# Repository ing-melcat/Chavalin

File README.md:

# Seguidor de Línea Pro v1 (ESP32-C3 + 16 Sensores + EDF 2S)

Proyecto de robot seguidor de línea velocista de 16 sensores basado en **ESP32-C3 SuperMini**, multiplexor analógico **CD74HC4067**, dos barras de sensores **QTR-8A** (versión china) dispuestas en **V (22°)**, driver de motores **TB6612FNG**, motores **JSumo 12V 3600 RPM**, llantas de silicón **Ø20 mm** y turbina **EDF 30 mm 14000KV** con alimentación independiente **2S (7.4V)**.

> **100% Libre de Wi-Fi / Bluetooth / RF:** Todo el proyecto opera de forma autónoma para cumplir el reglamento **RoboTiger Velocista Pro**. La calibración en banco y el ajuste fino de parámetros se realizan por **USB Serial (115200 baud)** con guardado automático en **Flash NVS (`Preferences`)**.

---

## Estructura del Repositorio

| Carpeta / Archivo | Descripción |
| :--- | :--- |
| `seguidor_pro/seguidor_pro.ino` | **Firmware único** de competencia (500 Hz exactos, `dt = 2 ms`), consola USB Serial de calibración/diagnóstico y persistencia NVS. |
| `test_turbina_nano/` | Sketch auxiliar de prueba PWM para ESC de turbina en Arduino Nano. |
| `v1/` | Esquemático y PCB base en KiCad (`v1.kicad_sch`, `v1.kicad_pcb`). |
| `v1_enrutado/` | PCB enrutado y vistas 3D de referencia. |

---

## Especificaciones de Hardware y Mapeo de Pines

- **Microcontrolador:** ESP32-C3 SuperMini (`esp32:esp32:nologo_esp32c3_super_mini`, `USB CDC On Boot = Enabled`).
- **Tracción:** 2× motores **JSumo 12V 3600 RPM**, rines de aluminio **Ø12 × 33 mm** (eje 3 mm) + gomas de silicón **Ø20 × 28 mm** (`Ø externa = 20 mm`).
- **Alimentación Principal (Tracción y Lógica):** LiPo **12V 750 mAh** directo a `VM` del TB6612 + regulador **step-down 12V→5V 3A** para alimentar el ESP32-C3.
- **Sistema Aerodinámico (Independiente):** Turbina **EDF 30 mm 14000KV** (~224 gf / 2.20 N de empuje máx.) + **ESC 35A** alimentados por batería aparte **7.4V (2S) 450 mAh** (cable rojo BEC del ESC desconectado; **GND común** con la placa).

| Subsistema | Señal / Función | Pin ESP32-C3 | Notas |
| :--- | :--- | :--- | :--- |
| **TB6612 (LEDC 20 kHz, 8 bits)** | `AI1` / `AI2` (Motor Izq A) | **GPIO 1**, **GPIO 2** | `PWMA`, `PWMB`, `STBY` fijos a `3.3V` |
| **TB6612 (LEDC 20 kHz, 8 bits)** | `BI1` / `BI2` (Motor Der B) | **GPIO 3**, **GPIO 8** | `GPIO 8` comparte LED azul integrado |
| **CD74HC4067 (Mux 16 ch)** | `SIG` / `COM` (Entrada ADC) | **GPIO 0** | Pull-down interno 45 kΩ forzado por registro |
| **CD74HC4067 (Mux 16 ch)** | `S0`, `S1`, `S2`, `S3` | **GPIO 20, 10, 7, 6** | `S0=20, S1=10, S2=7, S3=6`; `EN` (`~E`) fijo a `GND` |
| **Barras 2× QTR-8A (V 22°)** | `LED_ON` (Emisores IR) | **GPIO 4** | `HIGH` activo; `CH00..07` Barra 1, `CH08..15` Barra 2 |
| **Turbina EDF (LEDC 50 Hz)** | Señal PWM ESC (1000–2000 µs) | **GPIO 5** | Resolución 14 bits; armado seguro en `1000 µs` (0%) |
| **Arrancador Juez RRT** | Señal `GO` (`5V, GND, GO, RDY`) | **GPIO 21** | `INPUT_PULLDOWN`, antirrebote 3 lecturas a 500 Hz |
| **Calibración en Pista** | Botón físico `BOOT_CAL` | **GPIO 9** | `INPUT_PULLUP` (botón `BOOT` integrado) |

---

## Detalles Críticos de Ingeniería

1. **Anti-Saturación ADC en ESP32-C3 (`4095` Fijo):**
   El ADC con `ADC_11db` satura a **`2922 mV`**, mientras que las barras QTR-8A chinas tienen pull-ups (~15 kΩ a 3.3V) que las dejan entre `3.0 V` y `3.3 V`. En Arduino ESP32 v3.x, `analogReadMilliVolts()` reconfigura el pin y borra `pinMode(..., INPUT_PULLDOWN)`. Por ello el código ejecuta en `setup()`:
   - `analogReadMilliVolts(PIN_SIG);`
   - `gpio_pullup_dis((gpio_num_t)PIN_SIG);`
   - `gpio_pulldown_en((gpio_num_t)PIN_SIG);`
   Esto forma un divisor de voltaje (~`2483 mV` en reposo) dentro de la zona lineal del ADC.

2. **USB CDC No Bloqueante en Pista (`dt = 2 ms`):**
   Sin laptop conectada, escribir al puerto serie en ESP32-C3 puede bloquear el lazo de 500 Hz. El firmware usa `Serial.setTxTimeoutMs(0)`, verificación previa `Serial.availableForWrite()` y **pausa la telemetría periódica automáticamente durante la carrera**.

3. **Constantes Calibradas por Simulación Física (JSumo 3600 RPM + Ø20 mm + EDF 2S, 7/7 Escenarios):**
   Valores por defecto cargados cuando NVS está vacío (o al ejecutar `reset`):
   - `vr = 95` (velocidad recta), `vc = 58` (velocidad mínima en curva), `kf = 175` (freno en curva), `K_FRENO_DYN = 3.0`, `BRAKE_CAP = -195.0`, `MAX_PID = 175.0`.
   - `kpb = 0.34`, `kpc = 0.56` (ganancia cuadrática), `kd = 0.014` (`Kd_step = 7.00` a 2 ms, `ALPHA_D = 0.20`).
   - `tb = 50%` (recta), `tc = 80%` (curva cerrada), rampa de entrada 200 ms, decaimiento 160 ms (limitado a `[20%, 100%]` para no apagar la turbina en carrera).

---

## Compilación y Carga

- **Placa en Arduino IDE:** `NOLOGO ESP32C3 Super Mini` (`esp32:esp32:nologo_esp32c3_super_mini`)
- **USB CDC On Boot:** `Enabled` (`CDCOnBoot=cdc`)
- **Puerto:** `COM5` (o el COM asignado al conectar por USB-C)
- **Archivo único a abrir:** `seguidor_pro/seguidor_pro.ino`

---

## Calibración y Ajuste Fino por USB Serial (`115200 baud`)

Al conectar el robot a la PC (Monitor Serial a **115200**, funciona con `"Nueva línea"` o `"Sin ajuste de línea"`), dispones de consola interactiva sin recompilar:

| Comando | Acción |
| :--- | :--- |
| `c` | Autocalibra la base de los 16 sensores (percentil 75, ~1.2 s). Equivalente en pista al botón **`BOOT` (GPIO 9)**. |
| `v` | Activa / pausa la telemetría en vivo cada 250 ms (`S:[########|........] Err:+000 Turb: 0% GO:0`). |
| `t` (o `m`) | Test completo de motores (cuenta regresiva 3 s: A adelante, B adelante, ambos, reversa, giro en eje). |
| `1` / `2` | Prueba rápida 1 s solo Motor A (Izq) o Motor B (Der). |
| `u` | Prueba segura de turbina EDF al **25% durante 1.5 s** (sujetar robot; desconectar en `0%`). |
| `l` | Activa / desactiva el seguidor en banco (500 Hz + turbina). **Usar con el robot levantado o en pista controlada.** |
| `s` | **PARO DE EMERGENCIA inmediato** (detiene motores y apaga turbina al 0%, incluso en medio de una prueba o señal `GO`). |
| `p` o `?` | Muestra los parámetros actuales guardados en Flash NVS y el resumen de comandos. |
| `vr=95`, `vc=58`, `kf=175` | Ajusta velocidades / freno y guarda automáticamente en **Flash NVS**. |
| `kpb=0.34`, `kpc=0.56`, `kd=0.014` | Ajusta ganancias del PID dinámico y guarda automáticamente en **Flash NVS**. |
| `tb=50`, `tc=80` | Ajusta potencia base/curva de la turbina EDF (`20%..100%`) y guarda en **Flash NVS**. |
| `reset` | Restaura todas las constantes calibradas por defecto (`3600 RPM / Ø20 mm`) en Flash NVS. |

### Secuencia en Pista (Competencia)
1. Encender baterías (ESP32 arma el ESC de la turbina a `1000 µs` en `1 s` y realiza una autocalibración inicial).
2. Colocar el robot sobre el fondo de la pista y presionar **`BOOT` (GPIO 9)** si se requiere recalibrar la luz del coliseo (toma ~1.2 s, dentro de los 15 s previos).
3. Conectar o esperar señal positiva **`GO` (`GPIO 21`)** del módulo arrancador RRT del juez: el robot arranca en el lazo determinista de 500 Hz con turbina encendida y se detiene con freno activo cuando `GO` vuelve a `LOW`.

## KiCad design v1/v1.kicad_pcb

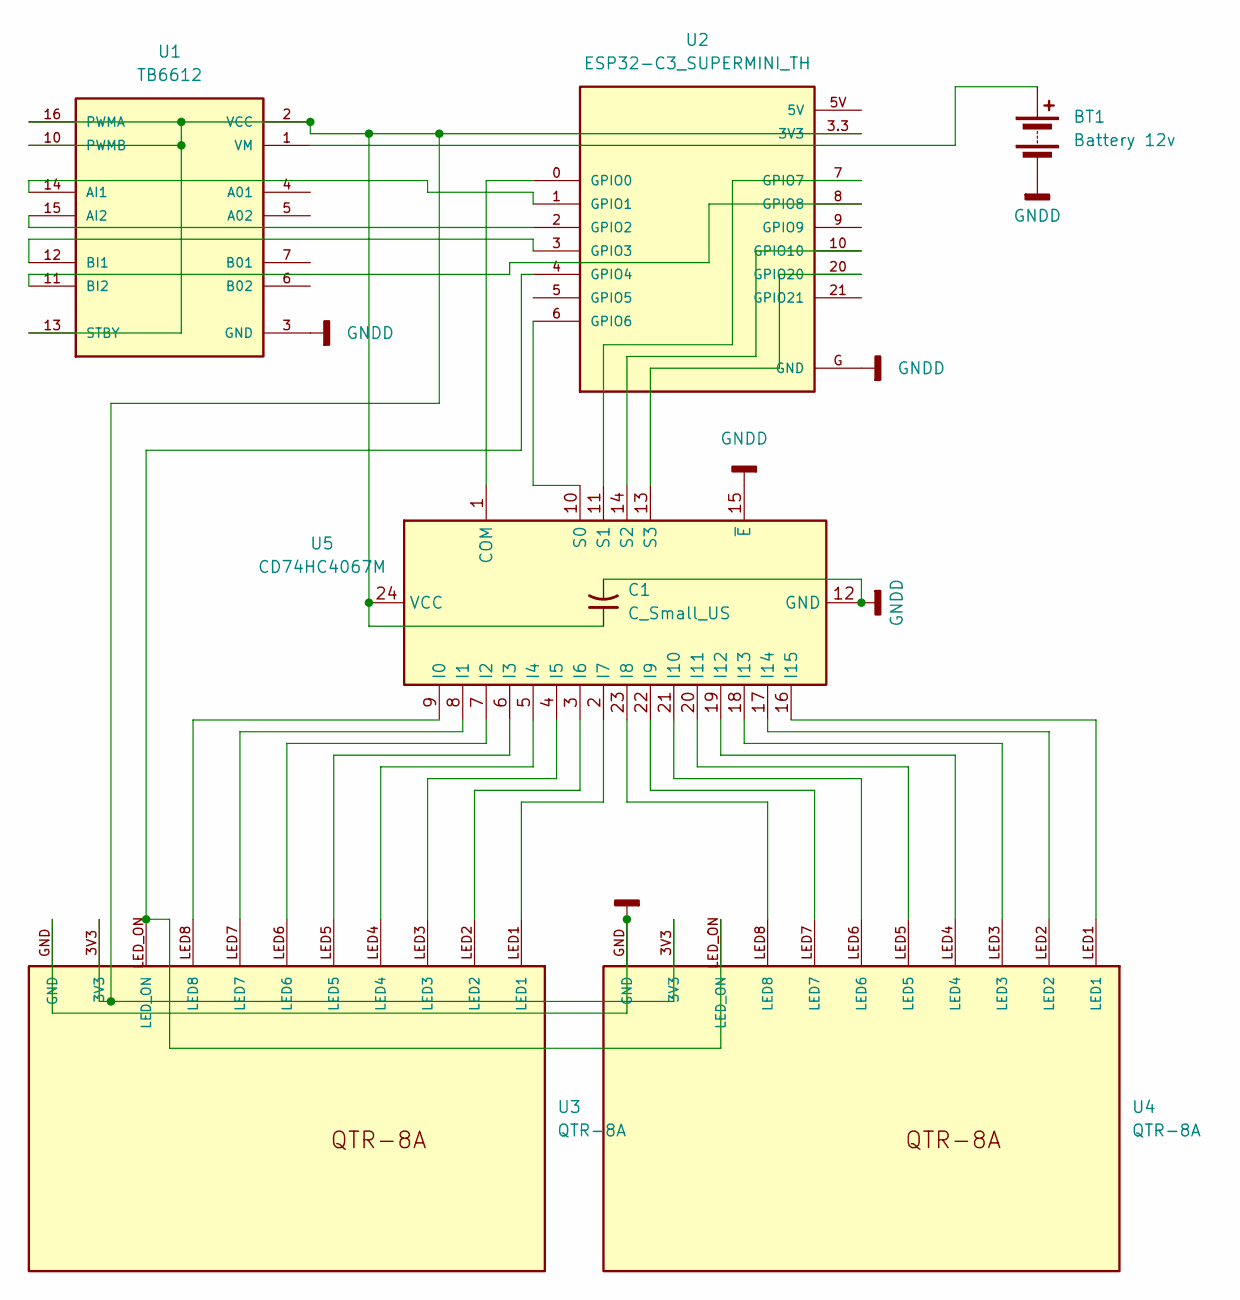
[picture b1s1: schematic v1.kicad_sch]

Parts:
BT1: Battery 12v; QFN-40-1EP_6x6mm_P0.5mm_EP4.6x4.6mm
C1: C_Small_US; SOIC-8_3.9x4.9mm_P1.27mm
U1: TB6612; MODULE_ROB-14450; MPN ROB-14450
U2: ESP32-C3_SUPERMINI_TH; MODULE_ESP32-C3_SUPERMINI_TH; MPN ESP32-C3 SuperMini_TH
U3, U4: QTR-8A; MPN QTR-8A
U5: CD74HC4067M; SOIC-24W_7.5x15.4mm_P1.27mm

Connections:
GNDD: BT1.2 (-), C1.2, U1.3 (GND), U1.8 (GND), U1.9 (GND), U2.G (GND), U3.GND, U4.GND, U5.12 (GND), U5.15 (~E)
unnamed: BT1.1 (+), U1.1 (VM)
unnamed: U1.14 (AI1), U2.1 (GPIO1)
unnamed: U1.15 (AI2), U2.2 (GPIO2)
unnamed: U1.12 (BI1), U2.3 (GPIO3)
unnamed: U1.11 (BI2), U2.8 (GPIO8)
unnamed: C1.1, U1.2 (VCC), U1.10 (PWMB), U1.13 (STBY), U1.16 (PWMA), U2.3.3 (3V3), U3.3V3, U4.3V3, U5.24 (VCC)
unnamed: U2.0 (GPIO0), U5.1 (COM)
unnamed: U2.4 (GPIO4), U3.LED_ON, U4.LED_ON
unnamed: U2.6 (GPIO6), U5.10 (S0)
unnamed: U2.7 (GPIO7), U5.11 (S1)
unnamed: U2.10 (GPIO10), U5.14 (S2)
unnamed: U2.20 (GPIO20), U5.13 (S3)
unnamed: U3.LED8, U5.9 (I0)
unnamed: U3.LED7, U5.8 (I1)
unnamed: U3.LED6, U5.7 (I2)
unnamed: U3.LED5, U5.6 (I3)
unnamed: U3.LED4, U5.5 (I4)
unnamed: U3.LED3, U5.4 (I5)
unnamed: U3.LED2, U5.3 (I6)
unnamed: U3.LED1, U5.2 (I7)
unnamed: U4.LED8, U5.23 (I8)
unnamed: U4.LED7, U5.22 (I9)
unnamed: U4.LED6, U5.21 (I10)
unnamed: U4.LED5, U5.20 (I11)
unnamed: U4.LED4, U5.19 (I12)
unnamed: U4.LED3, U5.18 (I13)
unnamed: U4.LED2, U5.17 (I14)
unnamed: U4.LED1, U5.16 (I15)

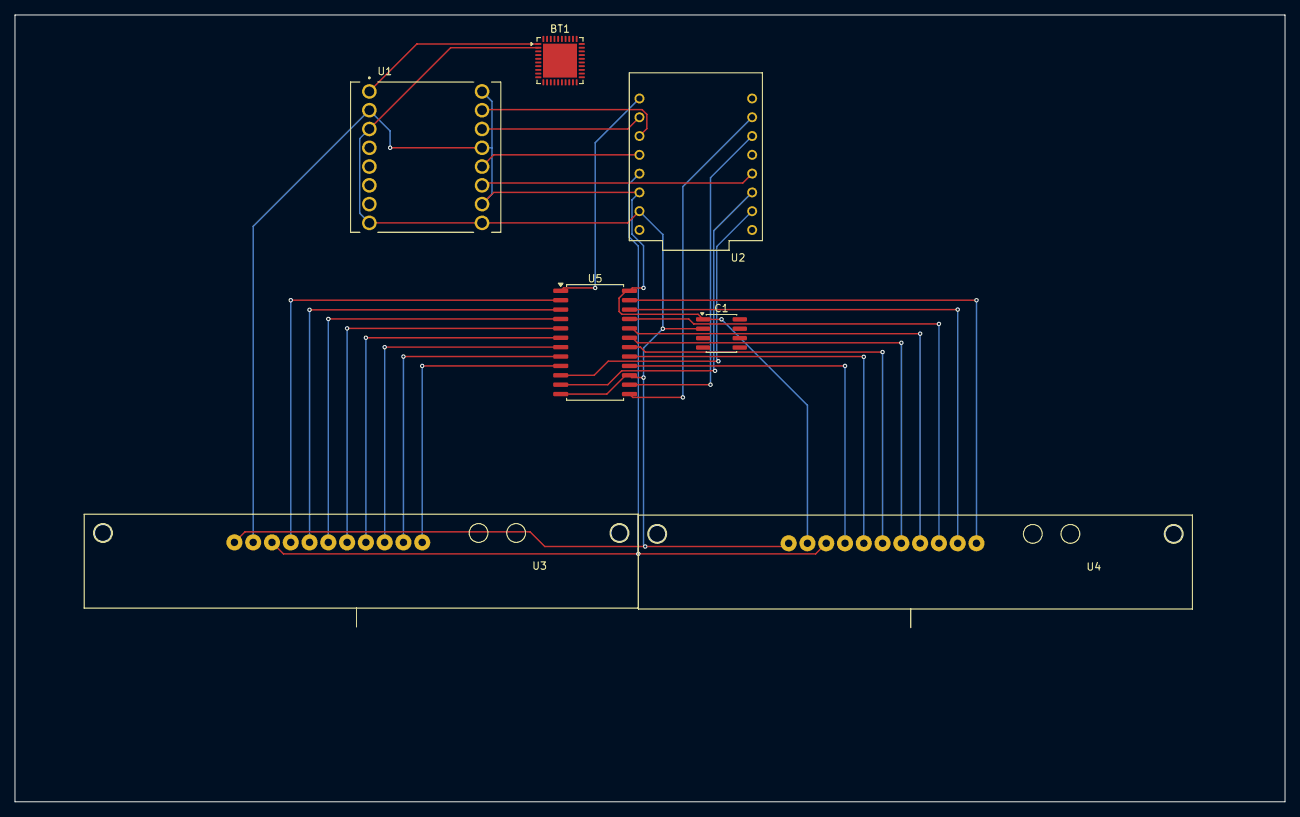
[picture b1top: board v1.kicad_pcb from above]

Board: 2 copper layers, 171.8 x 106.4 mm, 7 parts (0 on the bottom side), 29 nets.

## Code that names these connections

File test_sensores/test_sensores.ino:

/*
  =============================================================================
  PROYECTO: SEGUIDOR DE LINEA PRO - TEST DE SENSORES CON ANTI-SATURACIÓN ADC
  =============================================================================
  SOLUCIÓN AL PROBLEMA DE "TODO EN 4095":
  - El ADC del ESP32-C3 satura (topa en 4095) a los 2922 mV (2.92V).
  - Tus barras de sensores tienen resistencias pull-up a 3.3V (~15 kOhm), lo que
    mantiene el voltaje en reposo cerca de 3.30V (encima del tope de 2.92V).
  - Por eso, aunque el sensor baje de 3.30V a 2.95V al detectar color/luz, el
    ADC sin carga sigue marcando 4095 fijo.
  - Al mantener activo el Pull-Down interno de 45 kOhm por registro de hardware
    (gpio_pulldown_en) durante la conversión ADC, formamos un divisor de tensión
    que baja el reposo a ~2480 mV (dentro del rango lineal del ADC) y permite
    ver cualquier cambio en cada sensor.
  =============================================================================
*/

#include "driver/gpio.h"

#define PIN_SIG      0   // GPIO0: Entrada analógica conectada a SIG (COM) del Mux
#define PIN_S0      20   // GPIO20: Selector S0
#define PIN_S1      10   // GPIO10: Selector S1
#define PIN_S2       7   // GPIO7: Selector S2
#define PIN_S3       6   // GPIO6: Selector S3
#define PIN_LED_ON   4   // GPIO4: Encendido de emisores IR

// Sensibilidad en milivoltios respecto al reposo para marcar detección [█]
const int SENSIBILIDAD_MV = 20;

uint16_t lecturas_mv[16];
uint16_t base_mv[16];
bool calibrado = false;

void seleccionarCanal(uint8_t canal) {
  digitalWrite(PIN_S0, (canal & 0x01) ? HIGH : LOW);
  digitalWrite(PIN_S1, (canal & 0x02) ? HIGH : LOW);
  digitalWrite(PIN_S2, (canal & 0x04) ? HIGH : LOW);
  digitalWrite(PIN_S3, (canal & 0x08) ? HIGH : LOW);
  delayMicroseconds(30);
}

void leerSensoresMV() {
  // Asegurar que el Pull-Down de 45k esté activo en el pad para evitar saturación a 4095
  gpio_pullup_dis((gpio_num_t)PIN_SIG);
  gpio_pulldown_en((gpio_num_t)PIN_SIG);

  for (uint8_t ch = 0; ch < 16; ch++) {
    seleccionarCanal(ch);
    delayMicroseconds(100);
    // Promediar 4 muestras rápidas para eliminar ruido
    uint32_t suma = 0;
    for (int m = 0; m < 4; m++) {
      suma += analogReadMilliVolts(PIN_SIG);
    }
    lecturas_mv[ch] = suma / 4;
  }
}

void calibrarBase() {
  for (int i = 0; i < 16; i++) base_mv[i] = 0;
  for (int muestra = 0; muestra < 10; muestra++) {
    leerSensoresMV();
    for (int i = 0; i < 16; i++) {
      base_mv[i] += lecturas_mv[i];
    }
    delay(20);
  }
  for (int i = 0; i < 16; i++) {
    base_mv[i] /= 10;
  }
  calibrado = true;
}

void setup() {
  Serial.begin(115200);
  delay(1000);

  pinMode(PIN_S0, OUTPUT);
  pinMode(PIN_S1, OUTPUT);
  pinMode(PIN_S2, OUTPUT);
  pinMode(PIN_S3, OUTPUT);

  pinMode(PIN_LED_ON, OUTPUT);
  digitalWrite(PIN_LED_ON, HIGH);

  analogReadResolution(12);
  analogSetAttenuation(ADC_11db);

  // Inicializar el bus ADC en PIN_SIG primero y luego activar el Pull-Down por hardware
  analogReadMilliVolts(PIN_SIG);
  gpio_pullup_dis((gpio_num_t)PIN_SIG);
  gpio_pulldown_en((gpio_num_t)PIN_SIG);

  calibrarBase();
}

void loop() {
  leerSensoresMV();

  // Si el cable SIG se desconecta, con el Pull-Down caerá por debajo de 100 mV
  if (lecturas_mv[0] < 150 && lecturas_mv[7] < 150 && lecturas_mv[15] < 150) {
    Serial.println("[!] CABLE SIG DESCONECTADO O MUX SIN ALIMENTACION (Lectura: 0 mV)");
    delay(500);
    return;
  }

  Serial.println("------------------------------------------------------------------------------------------------------------------");
  Serial.println("CANAL:  | CH00  CH01  CH02  CH03  CH04  CH05  CH06  CH07 | CH08  CH09  CH10  CH11  CH12  CH13  CH14  CH15 |");
  Serial.println("SENSOR: | U3_S8 U3_S7 U3_S6 U3_S5 U3_S4 U3_S3 U3_S2 U3_S1 | U4_S8 U4_S7 U4_S6 U4_S5 U4_S4 U4_S3 U4_S2 U4_S1 |");
  Serial.println("------------------------------------------------------------------------------------------------------------------");

  // Mostrar voltaje real en mV (ya sin saturar en 4095)
  Serial.print("mV:     | ");
  for (int i = 0; i < 16; i++) {
    Serial.printf("%4d  ", lecturas_mv[i]);
    if (i == 7) Serial.print("| ");
  }
  Serial.println("|");

  // Mostrar diferencia (Delta) respecto al reposo
  Serial.print("CAMBIO: | ");
  for (int i = 0; i < 16; i++) {
    int diff = (int)lecturas_mv[i] - (int)base_mv[i];
    Serial.printf("%+4d  ", diff);
    if (i == 7) Serial.print("| ");
  }
  Serial.println("|");

  // Indicador visual cuando hay variación en el sensor
  Serial.print("DETECT: | ");
  for (int i = 0; i < 16; i++) {
    int diff = abs((int)lecturas_mv[i] - (int)base_mv[i]);
    if (diff >= SENSIBILIDAD_MV || lecturas_mv[i] < 2000) {
      Serial.print(" [█]  ");
    } else {
      Serial.print("  .   ");
    }
    if (i == 7) Serial.print("| ");
  }
  Serial.println("|");
  Serial.println("------------------------------------------------------------------------------------------------------------------\n");

  delay(200);
}

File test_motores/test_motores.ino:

/*
  =============================================================================
  TEST EXCLUSIVO DE MOTORES (TB6612FNG + ESP32-C3 SUPERMINI)
  =============================================================================
  Mapeo de pines (v1.kicad_sch):
    - AI1 (Motor Izquierdo / A) -> GPIO 1
    - AI2 (Motor Izquierdo / A) -> GPIO 2
    - BI1 (Motor Derecho / B)   -> GPIO 3
    - BI2 (Motor Derecho / B)   -> GPIO 8 (comparte con LED azul de la placa)
    - PWMA, PWMB, STBY          -> Fijos a 3.3V por hardware en PCB

  Método de control (PWM LEDC 20 kHz, 8 bits: 0..255):
    - Adelante: IN1 = PWM, IN2 = 0
    - Reversa:  IN1 = 0,   IN2 = PWM
    - Freno:    IN1 = 255, IN2 = 255
    - Paro:     IN1 = 0,   IN2 = 0

  Funcionamiento:
    - Inicia en modo MANUAL seguro (motores detenidos al arrancar).
    - Comandos por Monitor Serial (115200 baud):
        '1' -> Motor A (Izquierdo) ADELANTE (1.5 s)
        '2' -> Motor A (Izquierdo) REVERSA  (1.5 s)
        '3' -> Motor B (Derecho)   ADELANTE (1.5 s)
        '4' -> Motor B (Derecho)   REVERSA  (1.5 s)
        'w' -> AMBOS motores ADELANTE (1.5 s)
        'r' -> AMBOS motores REVERSA  (1.5 s)
        '+' / '-' -> Subir / bajar PWM de prueba (80..240)
        't' -> Iniciar ciclo automatico (5 fases)
        's' -> Paro inmediato / pausar ciclo
        'h' -> Mostrar menu de comandos
  =============================================================================
*/

#include <Arduino.h>

#define PIN_MOT_A1  1   // AI1: Motor Izquierdo (A)
#define PIN_MOT_A2  2   // AI2: Motor Izquierdo (A)
#define PIN_MOT_B1  3   // BI1: Motor Derecho (B)
#define PIN_MOT_B2  8   // BI2: Motor Derecho (B) - LED azul integrado

// Por seguridad mantenemos la turbina en 0% (1000 us) si el ESC está conectado en GPIO 5
#define PIN_TURBINA 5

const uint32_t PWM_FREQ = 20000;
const uint8_t  PWM_RES  = 8;

bool ciclo_automatico = false;
int  pwm_test = 160;
int  curA = 0;
int  curB = 0;

void setMotorA(int speed) {
  speed = constrain(speed, -255, 255);
  // Motor A (Izq) tiene polaridad física invertida en cableado: adelante = AI2 PWM
  if (speed > 0) {
    ledcWrite(PIN_MOT_A1, 0);
    ledcWrite(PIN_MOT_A2, speed);
  } else if (speed < 0) {
    ledcWrite(PIN_MOT_A1, -speed);
    ledcWrite(PIN_MOT_A2, 0);
  } else {
    ledcWrite(PIN_MOT_A1, 0);
    ledcWrite(PIN_MOT_A2, 0);
  }
}

void setMotorB(int speed) {
  speed = constrain(speed, -255, 255);
  if (speed > 0) {
    ledcWrite(PIN_MOT_B1, speed);
    ledcWrite(PIN_MOT_B2, 0);
  } else if (speed < 0) {
    ledcWrite(PIN_MOT_B1, 0);
    ledcWrite(PIN_MOT_B2, -speed);
  } else {
    ledcWrite(PIN_MOT_B1, 0);
    ledcWrite(PIN_MOT_B2, 0);
  }
}

void setMotors(int speedA, int speedB) {
  setMotorA(speedA);
  setMotorB(speedB);
}

void stopMotors() {
  setMotors(0, 0);
  curA = 0;
  curB = 0;
}

void irSuaveMotores(int tgtA, int tgtB) {
  while (curA != tgtA || curB != tgtB) {
    int nextA = tgtA;
    int nextB = tgtB;
    if ((curA > 0 && tgtA < 0) || (curA < 0 && tgtA > 0)) nextA = 0;
    if ((curB > 0 && tgtB < 0) || (curB < 0 && tgtB > 0)) nextB = 0;

    if (curA < nextA) curA = min(nextA, curA + 20);
    else if (curA > nextA) curA = max(nextA, curA - 20);

    if (curB < nextB) curB = min(nextB, curB + 20);
    else if (curB > nextB) curB = max(nextB, curB - 20);

    setMotors(curA, curB);
    delay(20);
  }
}

void brakeMotors() {
  ledcWrite(PIN_MOT_A1, 255);
  ledcWrite(PIN_MOT_A2, 255);
  ledcWrite(PIN_MOT_B1, 255);
  ledcWrite(PIN_MOT_B2, 255);
}

// Espera verificando si el usuario envía 's' para abortar al instante
bool esperarConAborto(uint32_t ms) {
  uint32_t inicio = millis();
  while (millis() - inicio < ms) {
    while (Serial.available() > 0) {
      char c = (char)Serial.read();
      if (c == 's' || c == 'S') {
        stopMotors();
        ciclo_automatico = false;
        Serial.println("\n>> [ALTO] Motores detenidos. Envia 't' para reanudar o '1'/'2'.");
        return false;
      }
    }
    delay(10);
  }
  return true;
}

void ejecutarSecuenciaMotores() {
  Serial.println("\n------------------------------------------------------");
  Serial.println(">> [1/5] MOTOR A (Izquierdo: GPIO 1/2) -> ADELANTE (PWM 140)");
  irSuaveMotores(140, 0);
  if (!esperarConAborto(1500)) return;
  irSuaveMotores(0, 0);
  if (!esperarConAborto(500)) return;

  Serial.println(">> [2/5] MOTOR A (Izquierdo: GPIO 1/2) -> REVERSA  (PWM -140)");
  irSuaveMotores(-140, 0);
  if (!esperarConAborto(1500)) return;
  irSuaveMotores(0, 0);
  if (!esperarConAborto(500)) return;

  Serial.println(">> [3/5] MOTOR B (Derecho:   GPIO 3/8) -> ADELANTE (PWM 140)");
  irSuaveMotores(0, 140);
  if (!esperarConAborto(1500)) return;
  irSuaveMotores(0, 0);
  if (!esperarConAborto(500)) return;

  Serial.println(">> [4/5] MOTOR B (Derecho:   GPIO 3/8) -> REVERSA  (PWM -140)");
  irSuaveMotores(0, -140);
  if (!esperarConAborto(1500)) return;
  irSuaveMotores(0, 0);
  if (!esperarConAborto(500)) return;

  Serial.println(">> [5/5] AMBOS MOTORES -> ADELANTE (PWM 160) + PARO SUAVE");
  irSuaveMotores(160, 160);
  if (!esperarConAborto(1500)) return;
  irSuaveMotores(0, 0);
  stopMotors();
  Serial.println(">> [OK] Ciclo terminado. Repitiendo en 3 s ('s' para detener)...");
}

void imprimirMenu() {
  Serial.println("\n======================================================");
  Serial.println("  TEST MANUAL DE MOTORES TB6612 - ESP32-C3 (COM5)");
  Serial.println("  Motor A (Izq): AI1=GPIO1, AI2=GPIO2");
  Serial.println("  Motor B (Der): BI1=GPIO3, BI2=GPIO8");
  Serial.printf ("  PWM actual: %d / 255 ('+' / '-' para ajustar)\n", pwm_test);
  Serial.println("  ------------------------------------------------------");
  Serial.println("  '1' = Motor IZQ ADELANTE | '2' = Motor IZQ REVERSA");
  Serial.println("  '3' = Motor DER ADELANTE | '4' = Motor DER REVERSA");
  Serial.println("  'w' = AMBOS ADELANTE     | 'r' = AMBOS REVERSA");
  Serial.println("  't' = Ciclo automatico   | 's' = PARO INMEDIATO");
  Serial.println("  'h' = Mostrar este menu");
  Serial.println("======================================================");
}

void probarManual(const char* desc, int sA, int sB, uint32_t ms) {
  ciclo_automatico = false;
  Serial.printf(">> [MANUAL PWM=%d] %s\n", pwm_test, desc);
  irSuaveMotores(sA, sB);
  if (esperarConAborto(ms)) {
    irSuaveMotores(0, 0);
    stopMotors();
    Serial.println(">> Detenido.");
  }
}

void setup() {
  Serial.begin(115200);
  Serial.setTxTimeoutMs(50);

  ledcAttach(PIN_MOT_A1, PWM_FREQ, PWM_RES);
  ledcAttach(PIN_MOT_A2, PWM_FREQ, PWM_RES);
  ledcAttach(PIN_MOT_B1, PWM_FREQ, PWM_RES);
  ledcAttach(PIN_MOT_B2, PWM_FREQ, PWM_RES);
  stopMotors();

  // Mantener ESC de turbina en 1000 us (0%) por seguridad
  ledcAttach(PIN_TURBINA, 50, 14);
  ledcWrite(PIN_TURBINA, (1000UL * 16383UL) / 20000UL);

  delay(1500);
  imprimirMenu();
  Serial.println("Modo MANUAL listo (motores detenidos). Envia un comando:");
}

void loop() {
  while (Serial.available() > 0) {
    char c = (char)Serial.read();
    if (c == 's' || c == 'S') {
      stopMotors();
      ciclo_automatico = false;
      Serial.println(">> [ALTO] Motores detenidos (PWM=0).");
    } else if (c == 't' || c == 'T') {
      ciclo_automatico = true;
      Serial.println(">> [AUTO] Iniciando ciclo automatico de motores...");
    } else if (c == '1') {
      probarManual("Motor A (Izquierdo) ADELANTE (1.5 s)...", pwm_test, 0, 1500);
    } else if (c == '2') {
      probarManual("Motor A (Izquierdo) REVERSA  (1.5 s)...", -pwm_test, 0, 1500);
    } else if (c == '3') {
      probarManual("Motor B (Derecho) ADELANTE (1.5 s)...", 0, pwm_test, 1500);
    } else if (c == '4') {
      probarManual("Motor B (Derecho) REVERSA  (1.5 s)...", 0, -pwm_test, 1500);
    } else if (c == 'w' || c == 'W') {
      probarManual("AMBOS motores ADELANTE (1.5 s)...", pwm_test, pwm_test, 1500);
    } else if (c == 'r' || c == 'R') {
      probarManual("AMBOS motores REVERSA  (1.5 s)...", -pwm_test, -pwm_test, 1500);
    } else if (c == '+') {
      pwm_test = constrain(pwm_test + 20, 80, 240);
      Serial.printf(">> PWM de prueba = %d / 255\n", pwm_test);
    } else if (c == '-') {
      pwm_test = constrain(pwm_test - 20, 80, 240);
      Serial.printf(">> PWM de prueba = %d / 255\n", pwm_test);
    } else if (c == 'h' || c == 'H' || c == '?') {
      imprimirMenu();
    }
  }

  if (ciclo_automatico) {
    ejecutarSecuenciaMotores();
    esperarConAborto(3000);
  } else {
    delay(20);
  }
}
